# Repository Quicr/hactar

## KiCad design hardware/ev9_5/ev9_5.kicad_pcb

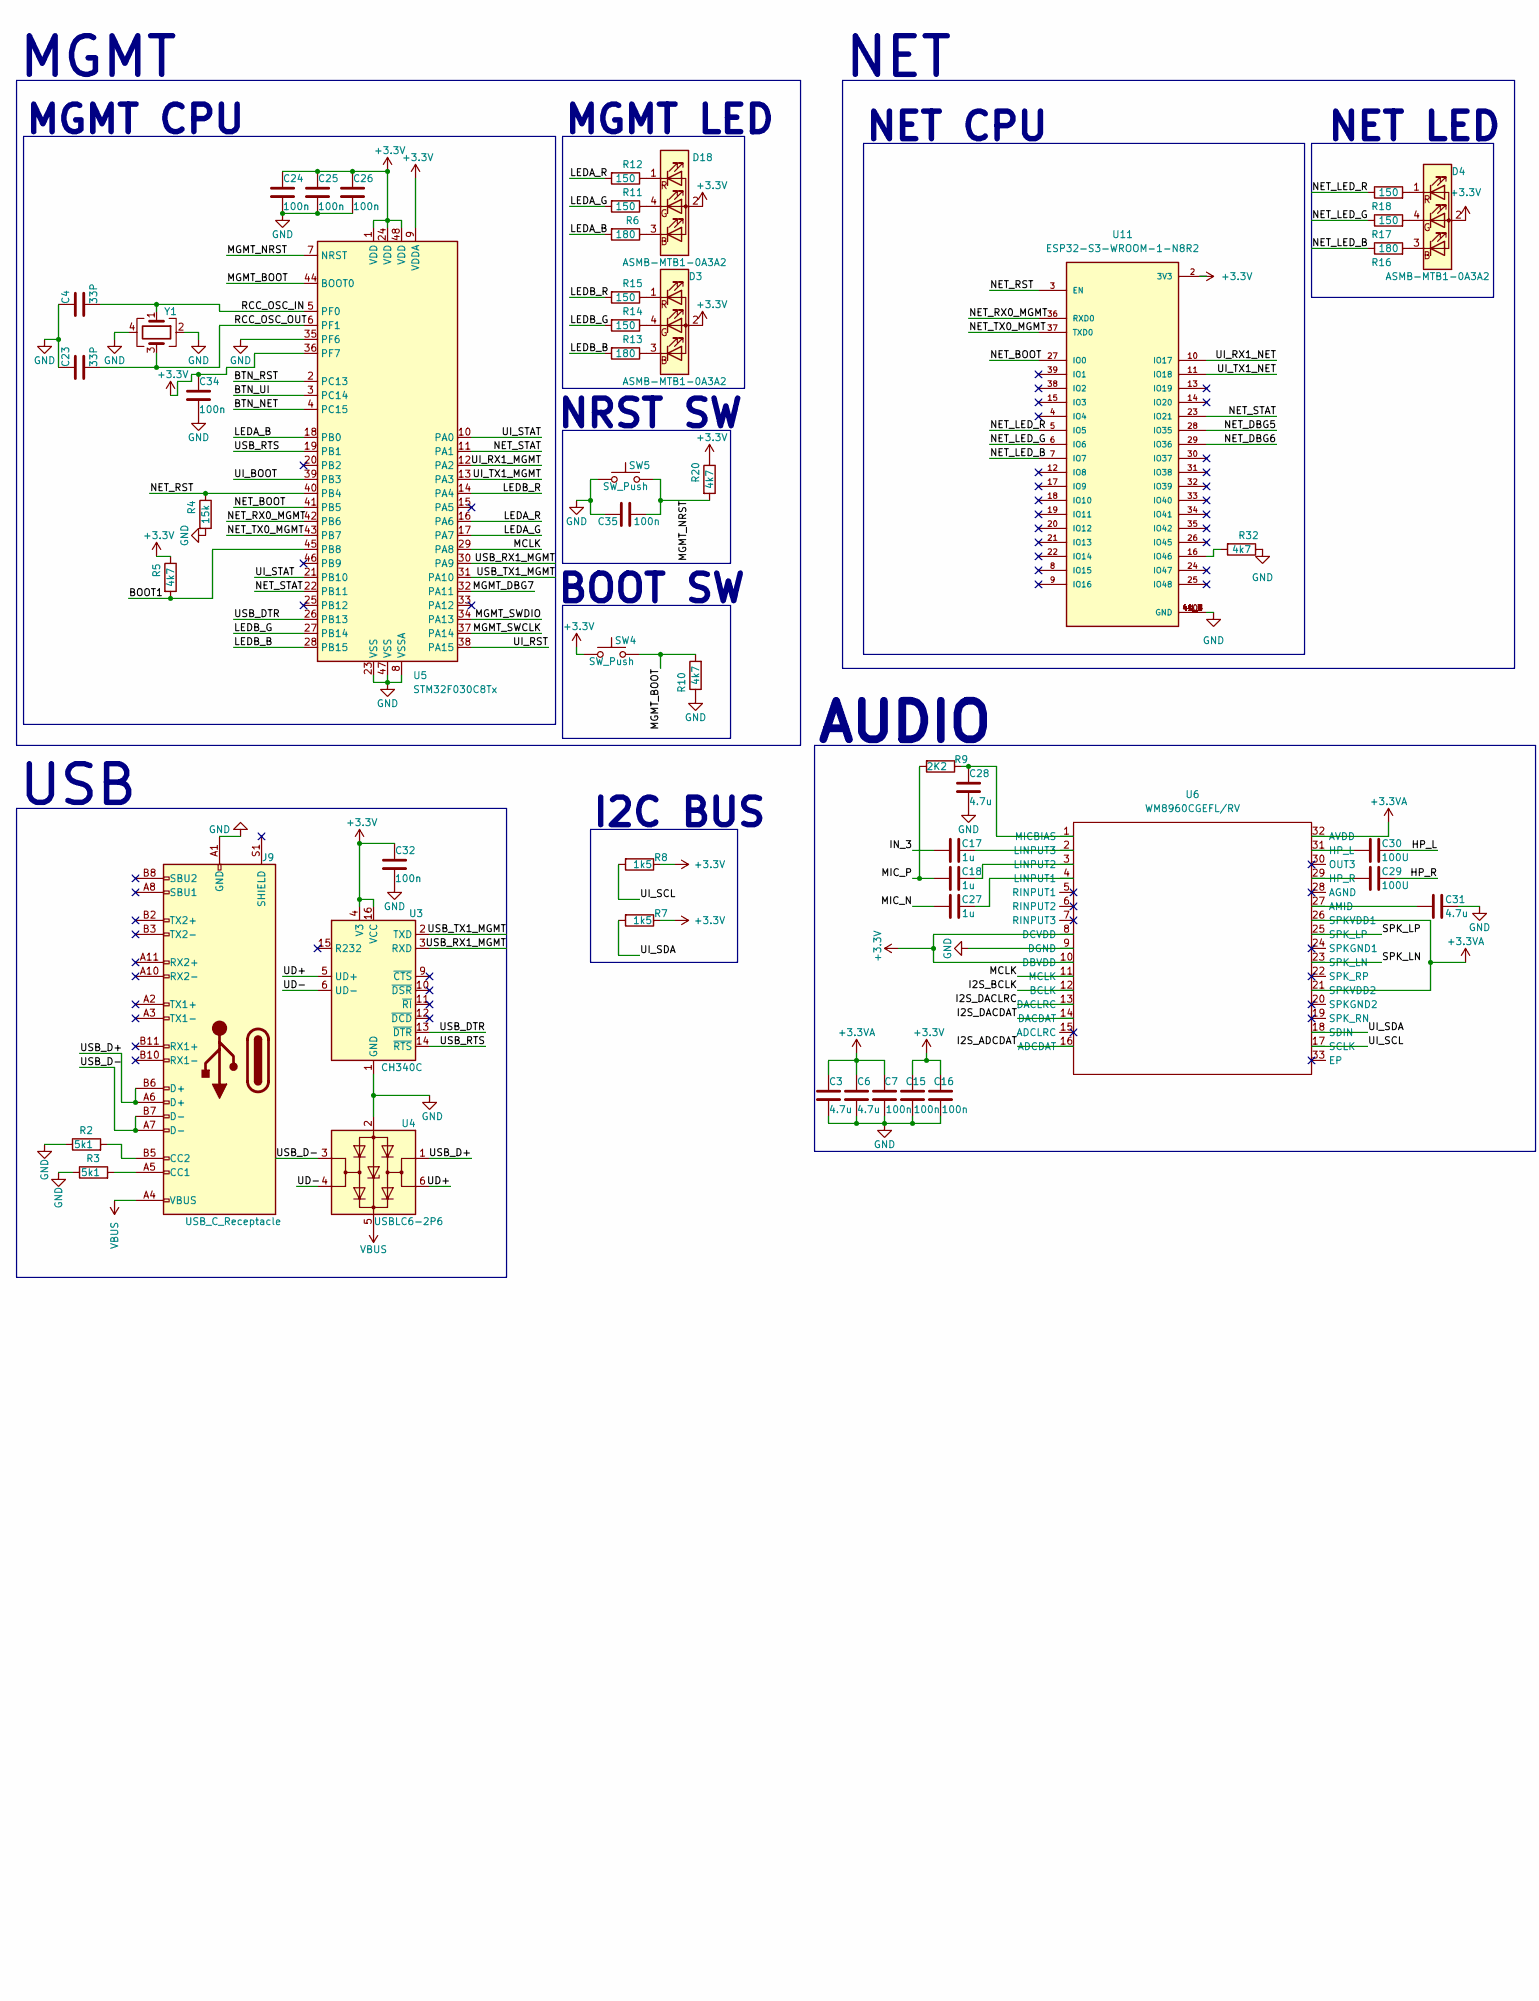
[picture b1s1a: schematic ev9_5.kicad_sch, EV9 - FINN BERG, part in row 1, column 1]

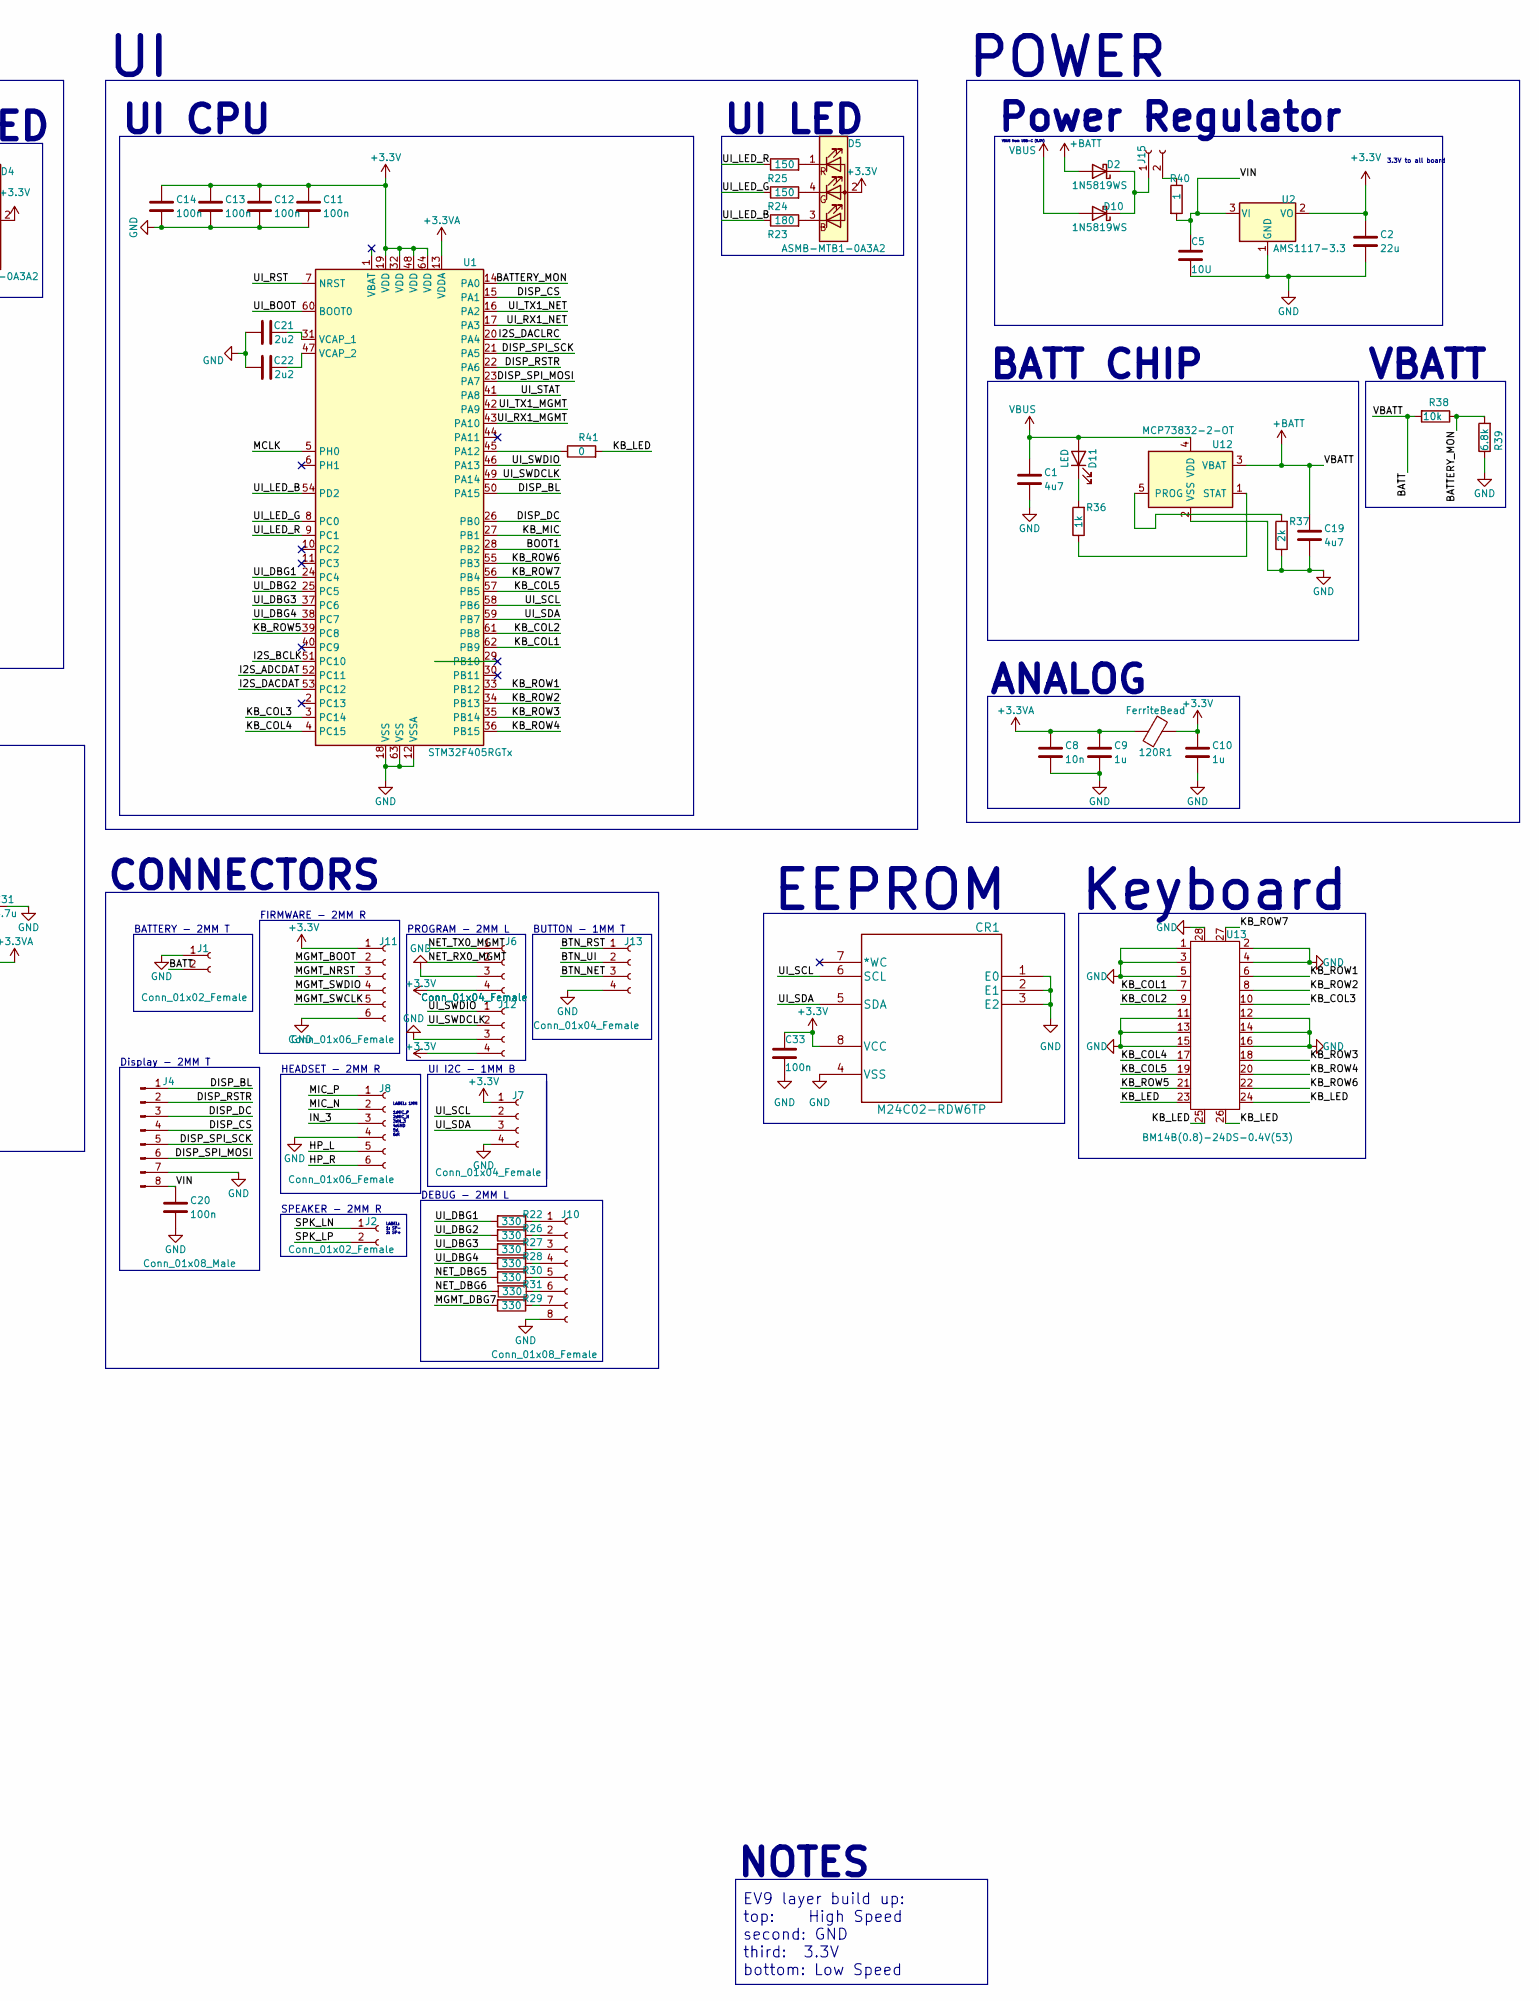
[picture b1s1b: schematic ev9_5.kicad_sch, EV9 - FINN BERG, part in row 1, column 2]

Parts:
120R1: FerriteBead; L_0603_1608Metric; JLCPCB# C127301
C1, C19: 4u7; C_0402_1005Metric; JLCPCB# C23733
C2: 22u; C_0805_2012Metric; JLCPCB# C45783
C3, C6, C28, C31: 4.7u; C_0402_1005Metric; JLCPCB# C23733
C4, C23: 33P; C_0805_2012Metric; JLCPCB# C107115
C5: 10U; C_0402_1005Metric; JLCPCB# C15525
C7, C11, C12, C13, C14, C15, C16, C20, C24, C25, C26, C32, C33, C34, C35: 100n; C_0402_1005Metric; JLCPCB# C1525
C8: 10n; C_0402_1005Metric; JLCPCB# C15195
C9, C10, C17, C18, C27: 1u; C_0402_1005Metric; JLCPCB# C52923
C21, C22: 2u2; C_0402_1005Metric; JLCPCB# C12530
C29, C30: 100U; C_1206_3216Metric; JLCPCB# C15008
CR1: M24C02-RDW6TP; New_ESP32_M24C02-RMN6TP; JLCPCB# C83836
D2, D10: 1N5819WS; D_SOD-323; JLCPCB# C191023
D3, D4, D5, D18: ASMB-MTB1-0A3A2; LED RGB; JLCPCB# C2874115
D11: LED; LED_0805_2012Metric; JLCPCB# C130114
J1, J2, J15: Conn_01x02_Female; JST_PH_S2B-PH-SM4-TB_1x02-1MP_P2.00mm_Horizontal; JLCPCB# C295747
J4: Conn_01x08_Male; PinHeader_1x08_P2.54mm_Vertical; JLCPCB# C2894931
J6, J7, J12, J13: Conn_01x04_Female; 1x4pin 1mm connector; JLCPCB# C3029343
J8, J11: Conn_01x06_Female; JST_PH_S6B-PH-SM4-TB_1x06-1MP_P2.00mm_Horizontal; JLCPCB# C265405
J9: USB_C_Receptacle; USB_C_Receptacle_HRO_TYPE-C-31-M-12; JLCPCB# C165948
J10: Conn_01x08_Female; JST_PH_S8B-PH-SM4-TB_1x08-1MP_P2.00mm_Horizontal; JLCPCB# C265121
R2, R3: 5k1; R_0402_1005Metric; JLCPCB# C25905
R4: 15k; R_0402_1005Metric; JLCPCB# C25756
R5, R10, R20, R32: 4k7; R_0402_1005Metric; JLCPCB# C25900
R6, R13, R16, R23: 180; R_0402_1005Metric; JLCPCB# C25087
R7, R8: 1k5; R_0402_1005Metric; JLCPCB# C25867
R9: 2K2; R_0402_1005Metric; JLCPCB# C25879
R11, R12, R14, R15, R17, R18, R24, R25: 150; R_0402_1005Metric; JLCPCB# C25082
R22, R26, R27, R28, R29, R30, R31: 330; R_0402_1005Metric; JLCPCB# C25104
R36: 1k; R_0402_1005Metric; JLCPCB# C11702
R37: 2k; R_0402_1005Metric; JLCPCB# C4109
R38: 10k; R_0402_1005Metric; JLCPCB# C25744
R39: 6.8k; R_0402_1005Metric; JLCPCB# C25917
R40: 1; R_0402_1005Metric; JLCPCB# C25086
R41: 0; R_0402_1005Metric; JLCPCB# C17168
SW4, SW5: SW_Push; SW_DIP_SPSTx01_Slide_6.7x4.1mm_W6.73mm_P2.54mm_LowProfile_J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; JLCPCB# C266189
U1: STM32F405RGTx; LQFP-64_10x10mm_P0.5mm; JLCPCB# C15742
U2: AMS1117-3.3; SOT-223-3_TabPin2; JLCPCB# C361784
U3: CH340C; SOIC-16_3.9x9.9mm_P1.27mm; JLCPCB# C84681
U4: USBLC6-2P6; SOT-666; JLCPCB# C2827693
U5: STM32F030C8Tx; LQFP-48_7x7mm_P0.5mm; JLCPCB# C80488
U6: WM8960CGEFL/RV; QFN50P500X500X90-33N; JLCPCB# C18752
U11: ESP32-S3-WROOM-1-N8R2; ESP32-S3-WROOM-1U; JLCPCB# C3013944
U12: MCP73832-2-OT; SOT-23-5; JLCPCB# C424093
U13: BM14B(0.8)-24DS-0.4V(53); BM14B(0.B)-24DS-0.4V(53)
Y1: Crystal_GND24; Crystal_SMD_3225-4Pin_3.2x2.5mm; JLCPCB# C13738

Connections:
+3.3V: 120R1.2, C2.1, C10.1, C11.1, C12.1, C13.1, C14.1, C15.2, C16.2, C24.1, C25.1, C26.1, C32.1, C33.1, C34.1, CR1.8 (VCC), D3.2 (A), D4.2 (A), D5.2 (A), D18.2 (A), J6.4, J7.1, J11.1, J12.4, R5.1, R7.1, R8.1, R20.1, SW4.2, U1.19 (VDD), U1.32 (VDD), U1.48 (VDD), U1.64 (VDD), U2.2 (VO), U3.4 (V3), U3.16 (VCC), U5.1 (VDD), U5.9 (VDDA), U5.24 (VDD), U5.36 (PF7), U5.48 (VDD), U6.8 (DCVDD), U6.10 (DBVDD), U11.2 (3V3)
+3.3VA: 120R1.1, C3.1, C6.1, C7.2, C8.1, C9.1, U1.13 (VDDA), U6.21 (SPKVDD2), U6.26 (SPKVDD1), U6.32 (AVDD)
+BATT: C19.1, D2.2 (A), J1.2, R38.2, U12.3 (VBAT)
/BATTERY_MON: R38.1, R39.2, U1.14 (PA0)
/BOOT1: R5.2, U1.28 (PB2), U5.45 (PB8)
/BTN_NET: J13.3, U5.4 (PC15)
/BTN_RST: J13.1, U5.2 (PC13)
/BTN_UI: J13.2, U5.3 (PC14)
/DISP_BL: J4.1, U1.50 (PA15)
/DISP_CS: J4.4, U1.15 (PA1)
/DISP_DC: J4.3, U1.26 (PB0)
/DISP_RSTR: J4.2, U1.22 (PA6)
/DISP_SPI_MOSI: J4.6, U1.23 (PA7)
/DISP_SPI_SCK: J4.5, U1.21 (PA5)
/HP_L: C30.2, J8.5
/HP_R: C29.2, J8.6
/I2S_ADCDAT: U1.52 (PC11), U6.16 (ADCDAT)
/I2S_BCLK: U1.51 (PC10), U6.12 (BCLK)
/I2S_DACDAT: U1.53 (PC12), U6.14 (DACDAT)
/I2S_DACLRC: U1.20 (PA4), U6.13 (DACLRC)
/IN_3: C17.1, J8.3
/KB_COL1: U1.62 (PB9), U13.7
/KB_COL2: U1.61 (PB8), U13.9
/KB_COL3: U1.3 (PC14), U13.10
/KB_COL4: U1.4 (PC15), U13.17
/KB_COL5: U1.57 (PB5), U13.19
/KB_LED: R41.2, U13.23, U13.24, U13.25, U13.26
/KB_MIC: U1.27 (PB1)
/KB_ROW1: U1.33 (PB12), U13.6
/KB_ROW2: U1.34 (PB13), U13.8
/KB_ROW3: U1.35 (PB14), U13.18
/KB_ROW4: U1.36 (PB15), U13.20
/KB_ROW5: U1.39 (PC8), U13.21
/KB_ROW6: U1.55 (PB3), U13.22
/KB_ROW7: U1.56 (PB4), U13.27
/LEDA_B: R6.2, U5.18 (PB0)
/LEDA_G: R11.2, U5.17 (PA7)
/LEDA_R: R12.2, U5.16 (PA6)
/LEDB_B: R13.2, U5.28 (PB15)
/LEDB_G: R14.2, U5.27 (PB14)
/LEDB_R: R15.2, U5.14 (PA4)
/MCLK: U1.5 (PH0), U5.29 (PA8), U6.11 (MCLK)
/MGMT_BOOT: J11.2, R10.2, SW4.1, U5.44 (BOOT0)
/MGMT_DBG7: R29.2, U5.32 (PA11)
/MGMT_NRST: C35.2, J11.3, R20.2, SW5.1, U5.7 (NRST)
/MGMT_SWCLK: J11.5, U5.37 (PA14)
/MGMT_SWDIO: J11.4, U5.34 (PA13)
/MIC_N: C27.1, J8.2
/MIC_P: C18.1, J8.1, R9.2
/NET_BOOT: U5.41 (PB5), U11.27 (IO0)
/NET_DBG5: R30.2, U11.28 (IO35)
/NET_DBG6: R31.2, U11.29 (IO36)
/NET_LED_B: R16.1, U11.7 (IO7)
/NET_LED_G: R17.1, U11.6 (IO6)
/NET_LED_R: R18.1, U11.5 (IO5)
/NET_RST: R4.1, U5.40 (PB4), U11.3 (EN)
/NET_RX0_MGMT: J6.2, U5.42 (PB6), U11.36 (RXD0)
/NET_STAT: U5.11 (PA1), U5.22 (PB11), U11.23 (IO21)
/NET_TX0_MGMT: J6.1, U5.43 (PB7), U11.37 (TXD0)
/RCC_OSC_IN: C4.2, U5.5 (PF0), Y1.1
/RCC_OSC_OUT: C23.2, U5.6 (PF1), Y1.3
/SPK_LN: J2.1, U6.23 (SPK_LN)
/SPK_LP: J2.2, U6.25 (SPK_LP)
/UD+: U3.5 (UD+), U4.6 (I/O1)
/UD-: U3.6 (UD-), U4.4 (I/O2)
/UI_BOOT: U1.60 (BOOT0), U5.39 (PB3)
/UI_DBG1: R22.2, U1.24 (PC4)
/UI_DBG2: R26.2, U1.25 (PC5)
/UI_DBG3: R27.2, U1.37 (PC6)
/UI_DBG4: R28.2, U1.38 (PC7)
/UI_LED_B: R23.1, U1.54 (PD2)
/UI_LED_G: R24.1, U1.8 (PC0)
/UI_LED_R: R25.1, U1.9 (PC1)
/UI_RST: U1.7 (NRST), U5.38 (PA15)
/UI_RX1_MGMT: U1.43 (PA10), U5.12 (PA2)
/UI_RX1_NET: U1.17 (PA3), U11.10 (IO17)
/UI_SCL: CR1.6 (SCL), J7.2, R8.2, U1.58 (PB6), U6.17 (SCLK)
/UI_SDA: CR1.5 (SDA), J7.3, R7.2, U1.59 (PB7), U6.18 (SDIN)
/UI_STAT: U1.41 (PA8), U5.10 (PA0), U5.21 (PB10)
/UI_SWDCLK: J12.2, U1.49 (PA14)
/UI_SWDIO: J12.1, U1.46 (PA13)
/UI_TX1_MGMT: U1.42 (PA9), U5.13 (PA3)
/UI_TX1_NET: U1.16 (PA2), U11.11 (IO18)
/USB_D+: J9.A6 (D+), J9.B6 (D+), U4.1 (I/O1)
/USB_D-: J9.A7 (D-), J9.B7 (D-), U4.3 (I/O2)
/USB_DTR: U3.13 (~DTR), U5.26 (PB13)
/USB_RTS: U3.14 (~RTS), U5.19 (PB1)
/USB_RX1_MGMT: U3.3 (RXD), U5.30 (PA9)
/USB_TX1_MGMT: U3.2 (TXD), U5.31 (PA10)
/VIN: C5.1, C20.1, J4.8, R40.2, U2.3 (VI)
GND: C1.2, C2.2, C3.2, C4.1, C5.2, C6.2, C7.1, C8.2, C9.2, C10.2, C11.2, C12.2, C13.2, C14.2, C15.1, C16.1, C19.2, C20.2, C21.1, C22.1, C23.1, C24.2, C25.2, C26.2, C28.2, C31.1, C32.2, C33.2, C34.2, C35.1, CR1.1 (E0), CR1.2 (E1), CR1.3 (E2), CR1.4 (VSS), J1.1, J4.7, J6.3, J7.4, J8.4, J9.A1 (GND), J9.A12 (GND), J9.B1 (GND), J9.B12 (GND), J10.8, J11.6, J12.3, J13.4, R2.1, R3.1, R4.2, R10.1, R32.1, R37.1, R39.1, SW5.2, U1.12 (VSSA), U1.18 (VSS), U1.63 (VSS), U2.1 (GND), U3.1 (GND), U4.2 (GND), U5.8 (VSSA), U5.23 (VSS), U5.35 (PF6), U5.47 (VSS), U6.9 (DGND), U11.1 (GND), U11.40 (GND), U11.41_1 (GND), U11.41_2 (GND), U11.41_3 (GND), U11.41_4 (GND), U11.41_5 (GND), U11.41_6 (GND), U11.41_7 (GND), U11.41_8 (GND), U11.41_9 (GND), U12.2 (VSS), U13.1, U13.2, U13.3, U13.4, U13.5, U13.11, U13.12, U13.13, U13.14, U13.15, U13.16, U13.28, Y1.2, Y1.4
unnamed: D3.3 (BK), R13.1
unnamed: D3.4 (GK), R14.1
unnamed: D3.1 (RK), R15.1
unnamed: D4.3 (BK), R16.2
unnamed: D4.4 (GK), R17.2
unnamed: D4.1 (RK), R18.2
unnamed: D5.3 (BK), R23.2
unnamed: D5.4 (GK), R24.2
unnamed: D5.1 (RK), R25.2
unnamed: D2.1 (K), D10.1 (K), J15.1
unnamed: D11.1 (K), R36.2
unnamed: D18.3 (BK), R6.1
unnamed: D18.4 (GK), R11.1
unnamed: D18.1 (RK), R12.1
unnamed: J9.A5 (CC1), R3.2
unnamed: J9.B5 (CC2), R2.2
unnamed: J10.1, R22.1
unnamed: J10.2, R26.1
unnamed: J10.3, R27.1
unnamed: J10.4, R28.1
unnamed: J10.5, R30.1
unnamed: J10.6, R31.1
unnamed: J10.7, R29.1
unnamed: J15.2, R40.1
unnamed: R41.1, U1.45 (PA12)
unnamed: C21.2, U1.31 (VCAP_1)
unnamed: C22.2, U1.47 (VCAP_2)
unnamed: C31.2, U6.27 (AMID)
unnamed: C30.1, U6.31 (HP_L)
unnamed: C29.1, U6.29 (HP_R)
unnamed: C27.2, U6.4 (LINPUT1)
unnamed: C18.2, U6.3 (LINPUT2)
unnamed: C17.2, U6.2 (LINPUT3)
unnamed: C28.1, R9.1, U6.1 (MICBIAS)
unnamed: R32.2, U11.16 (IO46)
unnamed: R37.2, U12.5 (PROG)
unnamed: R36.1, U12.1 (STAT)
VBUS: C1.1, D10.2 (A), D11.2 (A), J9.A4 (VBUS), J9.A9 (VBUS), J9.B4 (VBUS), J9.B9 (VBUS), U4.5 (VBUS), U12.4 (VDD)

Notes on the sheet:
MGMT
VBATT
SPEAKER - 2MM R
NET CPU
MGMT CPU
BATT CHIP
NET
POWER
PROGRAM - 2MM L
CONNECTORS
3.3V to all board
NET LED
UI CPU
HEADSET - 2MM R
NRST SW
BATTERY - 2MM T
BUTTON - 1MM T
EV9 layer build up: top: High Speed second: GND third: 3.3V bottom: Low Speed
LABEL: 1MM 1:MIC_P 2:MIC_N 3:IN_3 4:GND 5:L 6:R
AUDIO
BOOT SW
EEPROM
UI I2C - 1MM B
I2C BUS
FIRMWARE - 2MM R
USB
VBUS from USB-C (5.0V)
MGMT LED
LABEL: 1: SP- 2: SP+
NOTES
Power Regulator
Keyboard
Display - 2MM T
DEBUG - 2MM L
UI LED
ANALOG

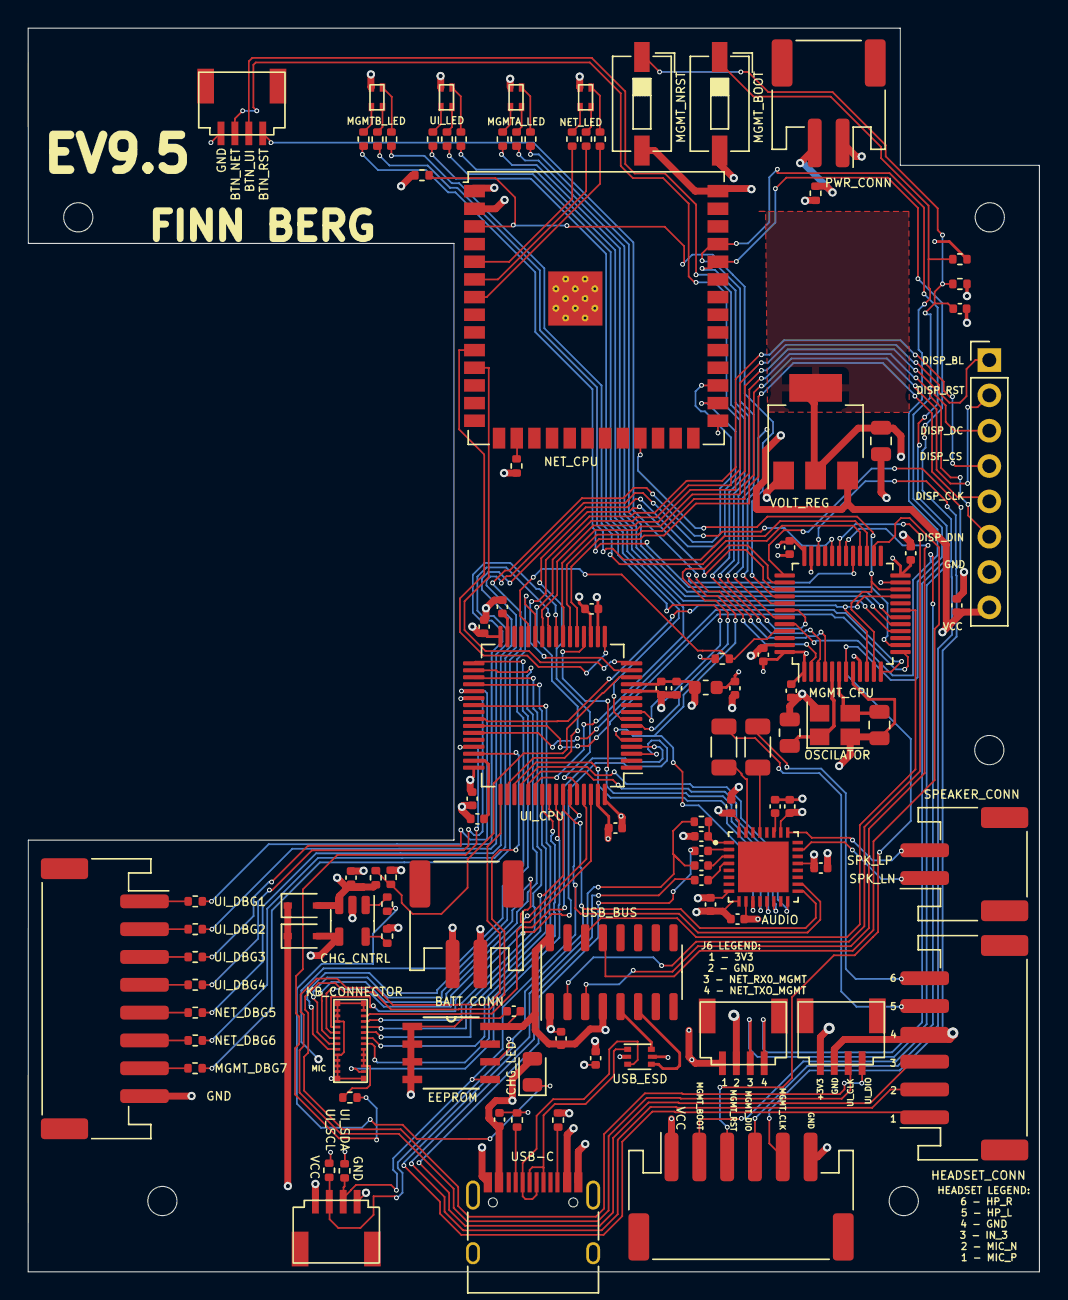
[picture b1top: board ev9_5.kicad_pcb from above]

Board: 4 copper layers, 72.7 x 89.4 mm, 103 parts (0 on the bottom side), 128 nets.

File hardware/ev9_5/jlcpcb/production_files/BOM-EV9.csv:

Comment,Designator,Footprint,LCSC
33P,"C23,C4",C_0805_2012Metric,C107115
1k,R36,R_0402_1005Metric,C11702
2u2,"C21,C22",C_0402_1005Metric,C12530
FerriteBead,120R1,L_0603_1608Metric,C127301
LED,D11,LED_0805_2012Metric,C130114
Crystal_GND24,Y1,Crystal_SMD_3225-4Pin_3.2x2.5mm,C13738
100U,"C29,C30",C_1206_3216Metric,C15008
10n,C8,C_0402_1005Metric,C15195
100n,"C11,C12,C13,C14,C15,C16,C20,C24,C25,C26,C32,C33,C34,C35,C7",C_0402_1005Metric,C1525
10U,C5,C_0402_1005Metric,C15525
STM32F405RGTx,U1,LQFP-64_10x10mm_P0.5mm,C15742
USB_C_Receptacle,J9,USB_C_Receptacle_HRO_TYPE-C-31-M-12,C165948
0,R41,R_0402_1005Metric,C17168
WM8960CGEFL/RV,U6,QFN50P500X500X90-33N,C18752
1N5819WS,"D10,D2",D_SOD-323,C191023
4u7,"C1,C19,C28,C3,C31,C6",C_0402_1005Metric,C23733
150,"R11,R12,R14,R15,R17,R18,R24,R25",R_0402_1005Metric,C25082
1,R40,R_0402_1005Metric,C25086
180,"R13,R16,R23,R6",R_0402_1005Metric,C25087
330,"R22,R26,R27,R28,R29,R30,R31",R_0402_1005Metric,C25104
10k,R38,R_0402_1005Metric,C25744
15k,R4,R_0402_1005Metric,C25756
1k5,"R7,R8",R_0402_1005Metric,C25867
2K2,R9,R_0402_1005Metric,C25879
4k7,"R10,R20,R32,R5",R_0402_1005Metric,C25900
5k1,"R2,R3",R_0402_1005Metric,C25905
6.8k,R39,R_0402_1005Metric,C25917
Conn_01x08_Female,J10,JST_PH_S8B-PH-SM4-TB_1x08-1MP_P2.00mm_Horizontal,C265121
Conn_01x06_Female,"J11,J8",JST_PH_S6B-PH-SM4-TB_1x06-1MP_P2.00mm_Horizontal,C265405
SW_Push,"SW4,SW5",SW_DIP_SPSTx01_Slide_6.7x4.1mm_W6.73mm_P2.54mm_LowProfile_JPin,C266189
USBLC6-2P6,U4,SOT-666,C2827693
ASMB-MTB1-0A3A2,"D18,D3,D4,D5",LED RGB,C2874115
Conn_01x08_Male,J4,PinHeader_1x08_P2.54mm_Vertical,C2894931
Conn_01x02_Female,"J1,J15,J2",JST_PH_S2B-PH-SM4-TB_1x02-1MP_P2.00mm_Horizontal,C295747
ESP32-S3-WROOM-1-N8R2,U11,ESP32-S3-WROOM-1U,C3013944
Conn_01x04_Female,"J12,J13,J6,J7",1x4pin 1mm connector,C3029343
AMS1117-3.3,U2,SOT-223-3_TabPin2,C361784
2k,R37,R_0402_1005Metric,C4109
MCP73832-2-OT,U12,SOT-23-5,C424093
22u,C2,C_0805_2012Metric,C45783
1u,"C10,C17,C18,C27,C9",C_0402_1005Metric,C52923
STM32F030C8Tx,U5,LQFP-48_7x7mm_P0.5mm,C80488
M24C02-RDW6TP,CR1,New_ESP32_M24C02-RMN6TP,C83836
CH340C,U3,SOIC-16_3.9x9.9mm_P1.27mm,C84681
BM14B(0.8)-24DS-0.4V(53),U13,BM14B(0.B)-24DS-0.4V(53),

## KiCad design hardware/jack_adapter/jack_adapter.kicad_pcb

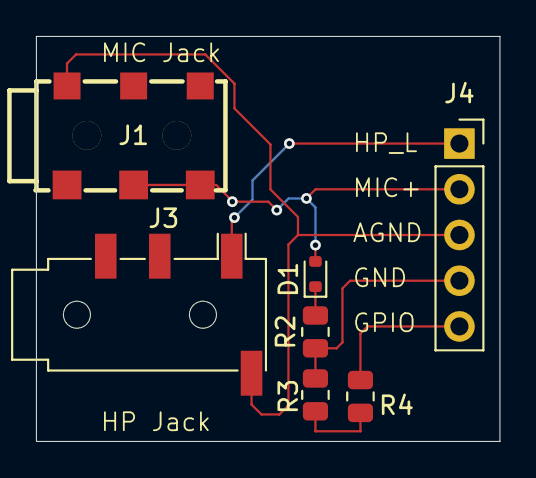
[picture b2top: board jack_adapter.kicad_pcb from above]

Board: 2 copper layers, 25.8 x 22.5 mm, 7 parts (0 on the bottom side), 7 nets.

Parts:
D1: 1N4148WT; D_SOD-523
J1: 2.5mm Mic; AUDIO-SMD_PJ-242D-SMT
J3: 3.5mm Headphones; Jack_3.5mm_PJ320D_Horizontal
J4: Header; PinSocket_1x05_P2.54mm_Vertical
R2: 51k; R_0805_2012Metric
R3: 100k; R_0805_2012Metric
R4: 10k; R_0805_2012Metric

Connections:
unnamed: D1.2 (A), J1.T, J4.2
unnamed: D1.1 (K), R2.2
unnamed: J3.T, J4.1
unnamed: J1.S, J3.S, J4.3
unnamed: J4.4, R2.1, R3.1
unnamed: J4.5, R4.1
unnamed: R3.2, R4.2
